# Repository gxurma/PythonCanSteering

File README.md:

# PythonCanSteering
PyQt4 Kvaser Canlib Can Middleware for steering Elmo Motion Cello 10/100 driven BLDC drives with openpnp

# Canlib
Canlib is taken from the Kvaser Canlib SDK. It is used as a wrapper to their library.

Tested with Kvaser Leaf Light 2

# Communication

The Cello are commanded over CAN bus with the SimplIQ commands.

Middleware talks to openpnp through a network socket.

The middleware periodically polls the position of all axes, and sends it to the openpnp

Middleware sends all M commands higher than 800 to the Smoothieboard.

# Homing

Homing is done simultaneously on all axes at the same time, after calling init().

How does homing work:

By pressing the Home button, the axis is driven with a defined jogSpeed to a mechanical stop, then the homing function is armed and the axis is travelling in the reverse direction with searchSpeed, slowly it searches for the index pulse.

X1 and Y is getting home position 0, Z gets the home position 100000, X2 gets the home position -4000, when it sees the index pulse.

C does not do the mechanical stop search, since that axis does not have one. It gets home position 744, so the nose of my tips is looking to the left.

# X axes
Since my machine has 2 X axes, where one of them is on the arm, and one of them is moving the desktop table, an algorithm had to be written to decide how to consistently and for openpnp transparently reach the specific points on the table. The goal is to extend the X travel possibilities.

It is currently set so that the table moves to 7500, 0 or -4600, depending on the overall sum X that needs to be reached.

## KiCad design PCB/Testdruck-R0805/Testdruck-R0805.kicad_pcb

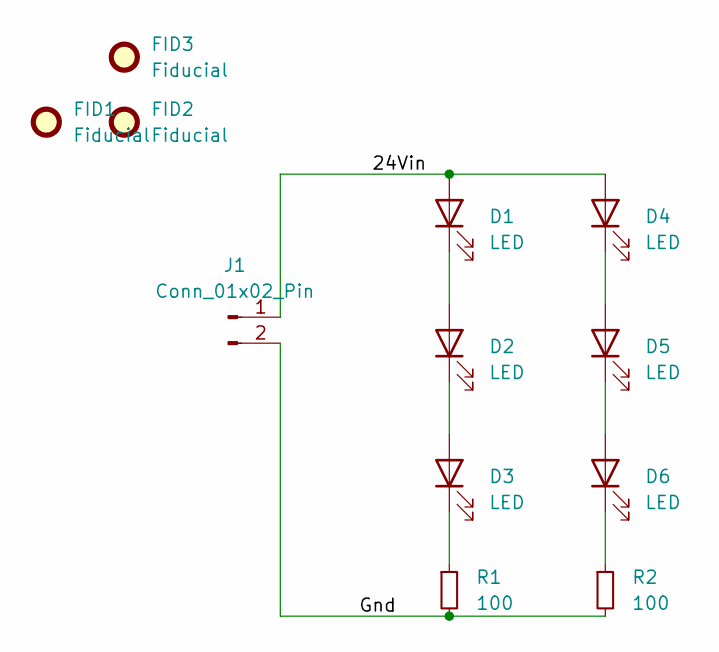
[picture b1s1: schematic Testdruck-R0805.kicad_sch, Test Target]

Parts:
D1, D2, D3, D4, D5, D6: LED; LED_PLCC_2835_Handsoldering
FID1, FID2, FID3: Fiducial; Fiducial_1mm_Mask2mm
J1: Conn_01x02_Pin; PinHeader_1x02_P1.00mm_Vertical
R1, R2: 100; R_0805_2012Metric

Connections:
/24Vin: D1.2 (A), D4.2 (A), J1.1
/Gnd: J1.2, R1.2, R2.2
unnamed: D1.1 (K), D2.2 (A)
unnamed: D2.1 (K), D3.2 (A)
unnamed: D3.1 (K), R1.1
unnamed: D4.1 (K), D5.2 (A)
unnamed: D5.1 (K), D6.2 (A)
unnamed: D6.1 (K), R2.1

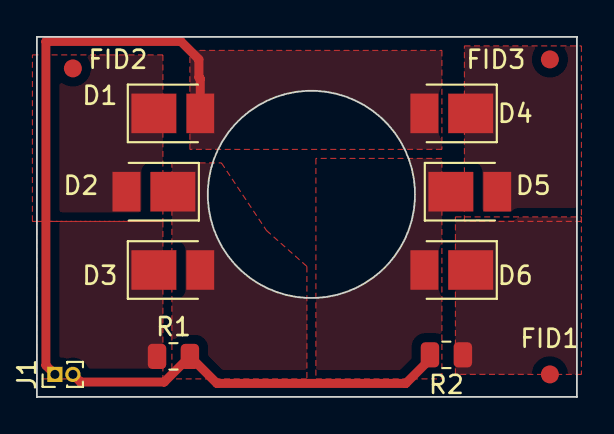
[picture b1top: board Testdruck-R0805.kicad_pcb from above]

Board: 2 copper layers, 30.0 x 20.0 mm, 12 parts (0 on the bottom side), 8 nets.

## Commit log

2019-03-18 changed readme
2019-03-18 added first codes
2019-03-18 added reference to kvaser
2019-04-03 Cleaning up just some old not needed stuff
2019-04-04 Deleted unnecessary stuff from gui and python script
2019-04-04 cleaned up lots of stuff, made some nice pages for testing and logs
2019-04-05 added teszt.py
2019-04-05 Now using new methods for commands
2019-04-06 added go method, cleaning homing methods
2019-04-06 really cleaned up homing methods
2019-04-06 timeout was too short
2019-04-06 added some pdfs so i do not loose them, and others can understand the commands, also added some text windows to the gui
2019-04-06 modified some buttons behaviour in Gui
2019-04-06 toggling Not Stop now releases all Motor An buttons
2019-04-08 added identifying of axes to the homing. now it should theoretically be possible to home simultaneously
2019-04-08 hope now it works.
2019-04-09 tried and corrected pos testing handles on machine
2019-04-11 added visual feedback to homing, now buttons show homing is in progress, until finished
2019-04-11 introduced go prepare and godo to make the starting of movement more synchronous
2019-04-11 added distance dependent handling of movement speed
2019-04-11 added home all button, since now every axe can home simultaneously
2019-04-11 added canlogging
2019-04-11 only works with isChecked
2019-04-12 only ischeched wrks
2019-04-15 added socket testing.
2019-04-15 testing socket operation
2019-04-17 developing position reports and other comms
2019-04-17 wasnt working as expected
2019-04-19 added queues but not yet using them
2019-04-19 trying out queues
2019-04-19 working visual feedback and movement sending to middleware
2019-04-19 added homing all axes to comm.
2019-04-20 just started serial usage
2019-05-02 now homing c to 744 counts to get nose to the correct position, and added machine.xml to git, to not loose it if pc crashes.
2019-05-02 some minor changes to position feedback usage, now it reports correct position, and added z -50 offset.
2019-05-02 just some serial testing
2019-05-02 trying somethin new with list of axes
2019-05-02 just some debugging with moving
2019-05-04 need to explicitly check for value 2, since if motor is off it gives 1, and it would think it is still moving...
2019-05-04 since doing something, not waiting anymore at homing
2019-05-06 trying to add acceleration to the go command.
2019-05-08 lets first try a global acceleration value
2019-05-08 encoding now the string, so serial write is not complaining anymore
2019-05-08 no serial test anymore
2019-05-10 no serial testing anymore
2019-05-10 first usage of tunneling to smoothie
2019-05-12 playing with accelerations and max speeds. Only problem is the x2. only likes 12500 max speed, and the acceleration should not be so high, because the parts ar being shifted due to high acceleration
2019-05-13 using table accelerations for smoother acc of x2, abd max x2 velocity to prevent motion stop because of pos error of x2
2019-05-15 added and tested tool changer events to project. works!
2019-05-15 added and tested tool changer events to project. works! again
2019-05-20 modified homing. G28 inits and homes every axis.
2019-05-21 homing all button is not checkable anymore
2019-05-21 added algorithm for usage of both x axes
2019-05-21 fixed bug, not movung if x target is 0.0
2019-05-21 fixed bug, not going to correct pos when going to x81.5
2019-05-21 corrected pos feedback sending to socket
2019-05-22 to be able to move over the uplooking cam...
2019-05-25 some problems with C
2019-05-25 Changed min and max to be able to use the correct ranges
2019-05-25 edited the readme.
2019-05-25 missing a constant change
2019-06-02 getting rid ofthe .5 rounding stuff, handing through the m messages to smoothie
2019-06-06 Added buttons for joystic and bCNC mode
2019-06-14 faster sending, and corrected serial adress
2019-06-20 pick failure due to multiple commands in one data packet
2019-06-20 next event of failure is reproducible
2019-06-20 now splitting at each newline also
2019-06-21 tested and repaired multiple command per package behaviour
2019-11-08 Added error handling of vanishing smoothie port
2019-11-24 initial openpnp2 machine setup
2019-12-25 added actuator buttons and indicators for pressure and touchdown
2019-12-25 added usbreset
2020-01-03 Köztes feltöltése az új funkcióknak
2020-01-03 first analysing of sensor data
2020-01-05 analysing pressure now works
2020-01-06 Already sending pressure data to socket
2020-01-07 added config from smoohieboard to be able to reproduce it if something bad happens
2020-01-07 connected pressure value to display. some warnings show up, due to safe threading etc.
2020-01-07 added handling of pushbuttons with a generic set Actuator function
2020-01-08 using signals to avoid failure due to not using main thread for displaying of sensor data
2020-01-08 now also able to match negative numbers in sensor data
2020-02-16 added linuxcan to be sure, it does not get lost. All credits go to Kvaser! They are the best USB to CAN bus converter company with their support
2020-02-16 not adding .o object files
2020-04-25 added test boards
2020-08-14 current state
2020-10-04 updated kvaser lib to fix build problems with new kernel
2020-10-06 removed X2 handling from Gcode
2020-10-06 fixed typo
2020-10-08 added new gui parts for postion handling
2020-10-09 added floating point display and joystic tab and positions tab
2020-10-09 Now also able to start without joystic
2020-10-09 added step handling for button move
2020-10-10 added button joystic usage
2020-10-10 added real joystic movement handling
2020-10-14 Verbessertes Joystic Verhalten
2020-10-14 modified z position indication to reflect openpnp position
2020-11-12 changing to PyQt5
2020-11-12 Gerüst für Positionsprg anbindung erstellt und verbunden)
2020-11-12 Laden und speichern)
2020-11-12 Capture
2020-11-13 first successful start with signals
2020-11-13 starting with go
2020-11-13 reverted joystic change
2020-11-13 Playback with Gcode implemented Achtung!
2020-11-13 Todos
2020-11-13 some changes in prg
2020-12-04 Erste Programme
2021-01-03 Getrennte Z und XY Bewegung, und Pause eingebaut
2021-01-05 testprogramme 20x Optik
2021-01-05 better Goto usage with threads
2021-01-05 some test programs
2021-01-29 Added test position programs
2021-03-11 Status gespeichert
2021-03-11 new buttons for moving C and fire jetter
2021-03-12 added C movement and Jet button usage
2021-03-12 commented out G28 there is no home all anymore
2021-03-12 some bugfixes
2021-03-13 modified for MKS-Sbase v1.3
2021-03-13 new config for MKS SBase v1.3
2021-03-14 added homeall to G28 command and some new indicators to Gui
2021-03-14 Reactivated sensor board, some changes in the readout of the endstops
2021-03-17 minor changes. added regex and command for sensor, added actuators
2021-03-19 ZCLamp actuation added
2021-03-19 added position reading command M114
2021-03-21 Some main changes
2021-03-22 added some example boards with virtual jetter parts
2023-07-26 something todo
2023-08-05 added jetter doku
2023-08-21 Added Dispenser assembly
2023-08-24 added model of nordson syringe barrel 5cc
2023-09-09 added theta elmo tuning params, now it is not vibrating
2023-09-20 neue config für dispenser Ventile
2023-09-20 Paar Änderungen im CAD
2023-09-20 Neue Daten und Todo Liste
2023-09-21 moved csv files to Grinder folder
2023-09-21 new config file due to using other pins for perifery
2023-09-21 ubuntu kernel updated, neededto recompile kvaser linuxcan3
2023-09-21 added new buttons for the dispensers and vacuum andling
2023-09-23 rearranged buttons, so it is easier to click on them
2023-09-27 Toolhalterhalter
2023-09-28 added toolchanger positions
2023-09-30 added feedback of actuators to represent what is going on if openpnp does send some command
2023-10-02 Restliche Feedbacks auch eingebaut
2023-10-02 added dispenser step files
2023-10-03 some cleaning
2023-10-03 had to retune C
2023-10-03 now using newest canlib library from kvaser. to install it use the pip whl from https://www.kvaser.com/download/?utm_source=software&utm_ean=7330130981911&utm_status=latest
2023-10-14 added homing improvement. now the velocity error must be eqal or bigger than the jogspeed, so the Z axis homes smoothly and does not stall and switch off
2023-11-18 added automatic tool changing usage, with actuating the tool changer valve too
2023-11-27 Added longer dispenser arm with more room
2023-11-27 lets try it
2023-12-09 added dispenser nozzles, calibrated dispenser positions
2023-12-09 Gui extended
2023-12-09 using thermal output 1
2023-12-12 added thermode temp function
2024-01-09 Heating setup v0.1
2024-01-09 Using bang bang for the bed. is better for our power supply
2024-01-11 added coefficients for thermistors andsome minor changes to gui
2024-02-12 added a dispenser test job
2024-02-12 some configs
2024-02-13 thermistor data updated
2024-02-14 korrigierte thermistor daten und Messung
2024-02-24 Added dispense commands
2024-02-25 had some tab mistakes
2024-02-25 lower hotend max temp, smaller bangbang
2024-03-01 Coefficients need no space
2024-03-09 Added PID tuned config overreide
2024-03-10 added new buttons
2024-03-13 Prelim. version of temp handling in gui
2024-03-13 Some tab errors
2024-03-13 Added reading out of temperatures
2024-03-23 Tool-6x6 mods
2024-03-23 Designs für Thermo Behandlung
2024-05-21 changed off temp to 37°C it can now reach it.
2024-05-23 Platte mit Jetter erweitert
2024-05-23 mal sehen ob ich beim Fahren gezielt dispensen kann
2024-05-23 doesnt want to directly close valve...
2024-05-24 changed timing of dispensing
2024-05-28 machine settings after calibration
2024-06-07 Added special tab
2024-06-08 Added usage of extra thread for handling the analysis and movements, so that the readback and motion sensing information is correct and drawing with gcode is possible
2024-06-08 some calibrations redone
2024-06-13 added some examples for the drawing of islands, still needs to be improved
2024-06-14 some new patterns
2024-06-18 Halbwegs brauchbare Offset Verwendung
2024-06-18 added emergency stop function to escape and space button
2024-07-08 enhanced joystic usage control display
2024-07-10 faster readout of pos
2024-07-21 added Testdruck
2024-07-21 example added
2024-07-22 Added printer usage
2024-07-22 handling mess
2024-07-25 first full jet, pick, alignment and place with table movement using event scripts
2024-07-31 Whatever was changed on gui
2024-07-31 Machine Thermode Offset adjusted
2024-07-31 some kvaser linuxcan stuff added
2025-12-22 added new canlib from kvaser
2026-01-28 added Prof. Setup
2026-01-29 had some new kvaser stuff
2026-01-29 prof now QFN56 infineon Chip too

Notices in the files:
PCB/Testdruck-R0805/Testdruck-R0805.kicad_pcb:
(c) 2024-07-19
